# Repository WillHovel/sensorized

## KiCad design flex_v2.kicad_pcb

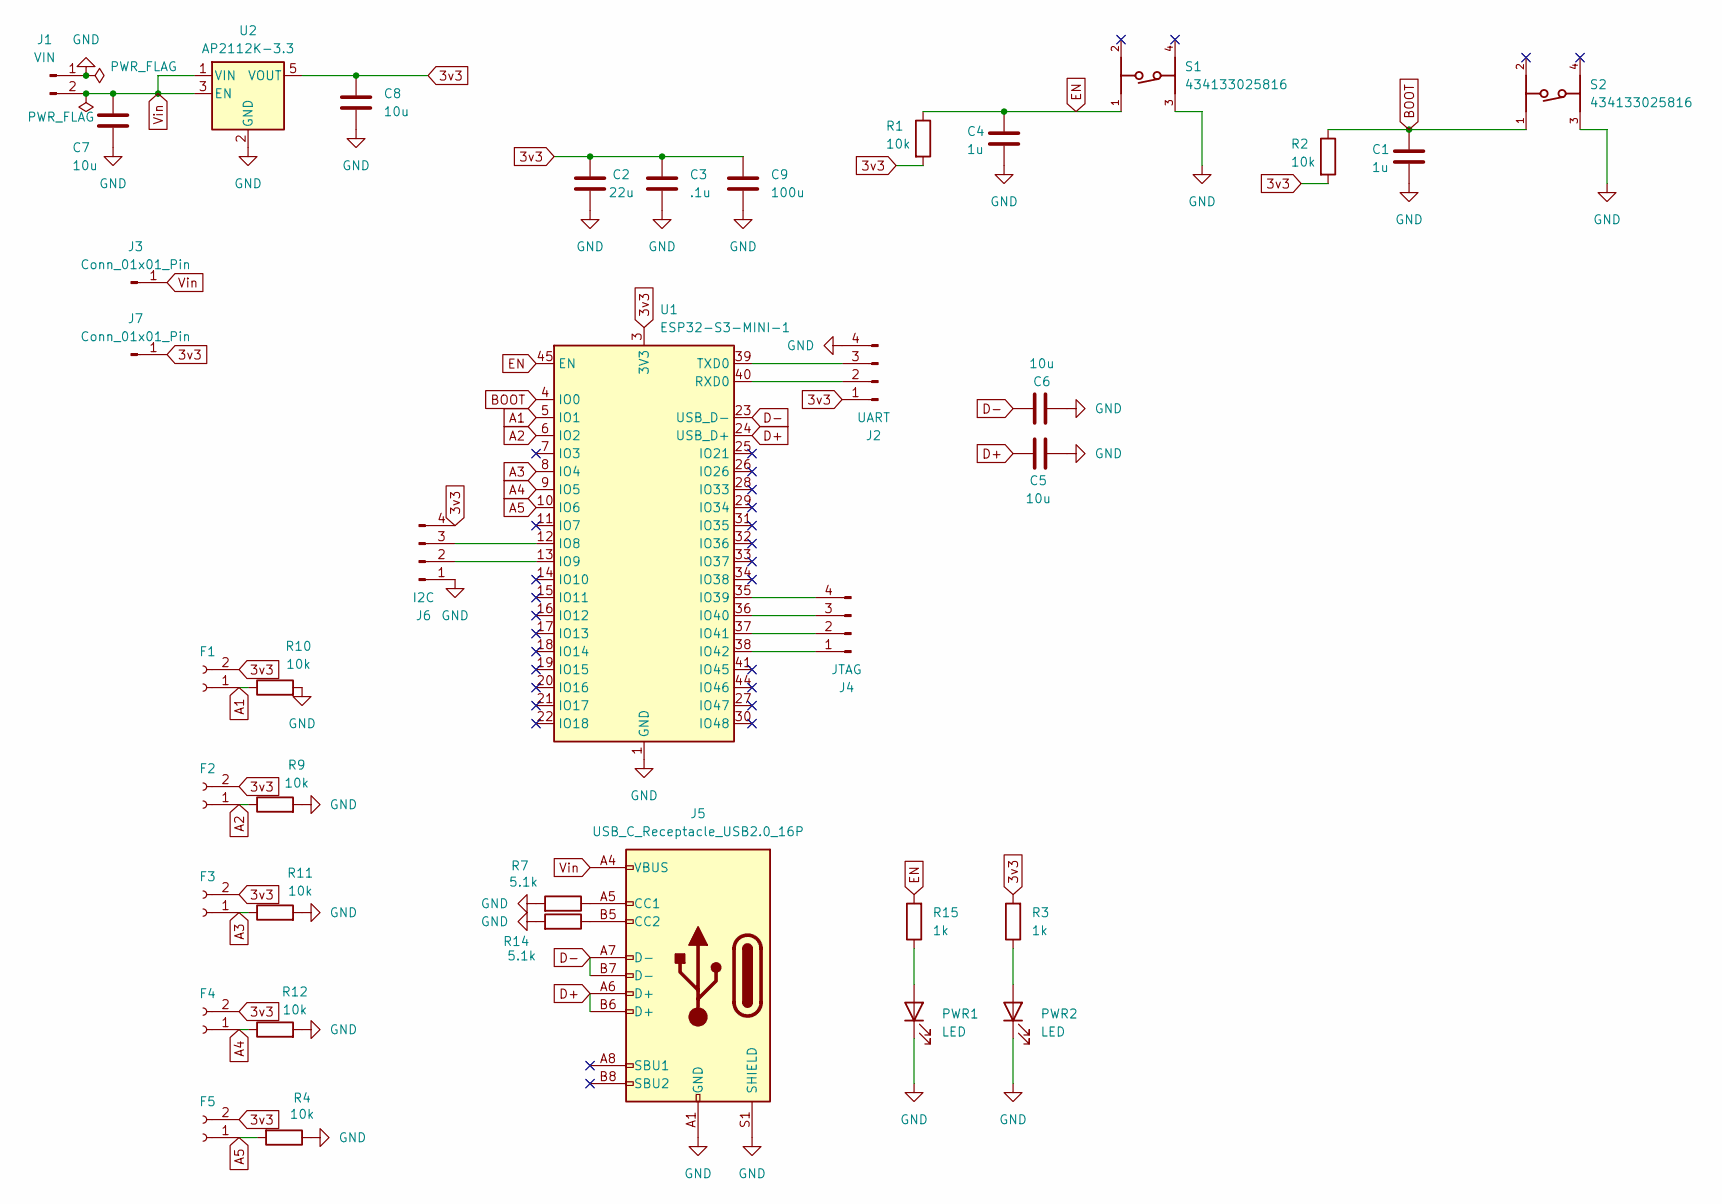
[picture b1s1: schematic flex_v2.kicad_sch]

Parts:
C1, C4: 1u; C_0603_1608Metric_Pad1.08x0.95mm_HandSolder
C2: 22u; C_0603_1608Metric_Pad1.08x0.95mm_HandSolder
C3: .1u; C_0603_1608Metric_Pad1.08x0.95mm_HandSolder
C5, C6, C7, C8: 10u; C_0603_1608Metric_Pad1.08x0.95mm_HandSolder
C9: 100u; C_0603_1608Metric_Pad1.08x0.95mm_HandSolder
F1, F2, F3, F4, F5: Conn_01x02_Socket; PinSocket_1x02_P2.54mm_Vertical
J1: VIN; PinHeader_1x02_P2.54mm_Vertical
J2: UART; PinHeader_1x04_P2.54mm_Vertical
J3, J7: Conn_01x01_Pin; PinHeader_1x01_P2.54mm_Vertical
J4: JTAG; PinHeader_1x04_P2.54mm_Vertical
J5: USB_C_Receptacle_USB2.0_16P; USB_C_Receptacle_GCT_USB4105-xx-A_16P_TopMnt_Horizontal
J6: I2C; PinHeader_1x04_P2.54mm_Vertical
PWR1, PWR2: LED; LED_0805_2012Metric_Pad1.15x1.40mm_HandSolder
R1, R2, R4, R9, R10, R11, R12: 10k; R_0603_1608Metric_Pad0.98x0.95mm_HandSolder
R3, R15: 1k; R_0603_1608Metric_Pad0.98x0.95mm_HandSolder
R7, R14: 5.1k; R_0603_1608Metric_Pad0.98x0.95mm_HandSolder
S1, S2: 434133025816
U1: ESP32-S3-MINI-1; ESP32-S2-MINI-1
U2: AP2112K-3.3; SOT-23-5

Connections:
3v3: C2.1, C3.1, C8.1, C9.1, F1.2, F2.2, F3.2, F4.2, F5.2, J2.1, J6.4, J7.1, R1.2, R2.2, R3.2, U1.3 (3V3), U2.5 (VOUT)
A1: F1.1, R10.1, U1.5 (IO1)
A2: F2.1, R9.1, U1.6 (IO2)
A3: F3.1, R11.1, U1.8 (IO4)
A4: F4.1, R12.1, U1.9 (IO5)
A5: F5.1, R4.2, U1.10 (IO6)
BOOT: C1.2, R2.1, S2.1, U1.4 (IO0)
D+: C5.1, J5.A6 (D+), J5.B6 (D+), U1.24 (USB_D+)
D-: C6.2, J5.A7 (D-), J5.B7 (D-), U1.23 (USB_D-)
EN: C4.2, R1.1, R15.2, S1.1, U1.45 (EN)
GND: C1.1, C2.2, C3.2, C4.1, C5.2, C6.1, C7.2, C8.2, C9.2, J1.1, J2.4, J5.A1 (GND), J5.A12 (GND), J5.B1 (GND), J5.B12 (GND), J5.S1 (SHIELD), J6.1, PWR1.1 (K), PWR2.1 (K), R4.1, R7.2, R9.2, R10.2, R11.2, R12.2, R14.2, S1.3, S2.3, U1.1 (GND), U1.2 (GND), U1.42 (GND), U1.43 (GND), U1.46 (GND), U1.47 (GND), U1.48 (GND), U1.49 (GND), U1.50 (GND), U1.51 (GND), U1.52 (GND), U1.53 (GND), U1.54 (GND), U1.55 (GND), U1.56 (GND), U1.57 (GND), U1.58 (GND), U1.59 (GND), U1.60 (GND), U1.61 (GND), U1.62 (GND), U1.63 (GND), U1.64 (GND), U1.65 (GND), U2.2 (GND)
unnamed: J2.2, U1.40 (RXD0)
unnamed: J2.3, U1.39 (TXD0)
unnamed: J4.1, U1.38 (IO42)
unnamed: J4.2, U1.37 (IO41)
unnamed: J4.3, U1.36 (IO40)
unnamed: J4.4, U1.35 (IO39)
unnamed: J5.A5 (CC1), R7.1
unnamed: J5.B5 (CC2), R14.1
unnamed: J6.2, U1.13 (IO9)
unnamed: J6.3, U1.12 (IO8)
unnamed: PWR1.2 (A), R15.1
unnamed: PWR2.2 (A), R3.1
Vin: C7.1, J1.2, J3.1, J5.A4 (VBUS), J5.A9 (VBUS), J5.B4 (VBUS), J5.B9 (VBUS), U2.1 (VIN), U2.3 (EN)

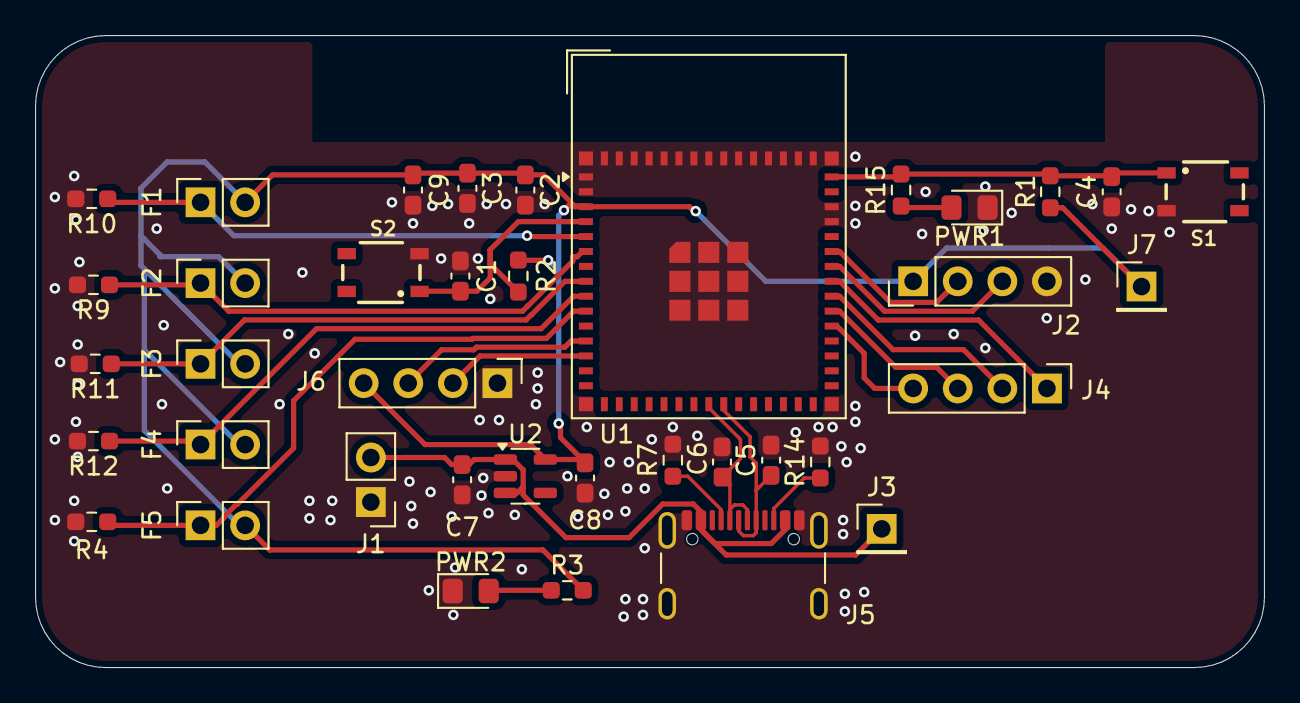
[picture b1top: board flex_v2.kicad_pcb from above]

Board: 2 copper layers, 70.0 x 36.0 mm, 38 parts (0 on the bottom side), 24 nets.
